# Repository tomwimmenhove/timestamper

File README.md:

# The Timestamper

This project lets you get get exact timestamps of 'events' (electric pulses on an input).

## Hardware
The hardware (schematic and PCB) are designed in KiCad 5, and can be found in the ./hardware/cpld/ directory. The 'heart'
of the design is a Xilinx XC9572XL CPLD. This CPLD implements a capture-counter which timestamps the arrival of events
with a resolution of 10ns. This CPLD is programmed in VHDL using Xilinx's ISE 14.7 (https://www.xilinx.com/support/download/index.html/content/xilinx/en/downloadNav/design-tools/v2012_4---14_7.html).

The VHDL project resides in the ./hardware/cpld/ directory. The XC9572XL can be programmed using the xc3sprog (http://xc3sprog.sourceforge.net/) utility.
Both the 'ft232h' (with a serial FT232H UART chip) and the 'sysfsgpio' (sysfsgpio on the Raspberry Pi) have been
successfully used to program the chip.

## Firmware
The firmware runs on an Atmel Atmega328p, which makes it compatible with the arduino. This way, using the default bootloader for,
for example, the Arduino pro mini 3.3v @8Mhz, we can easily program the firmware using avrdude. The firmware simply reads the
captured values from the CPLD and passes them on to a CH340G serial to USB UART. The firmware can be found in ./firmware/atmega328/

## Software
The software just outputs the values from the device onto stdout. See ./software/

# Theory of operation
The board is fed 3 signals:
 - A (very stable) 10MHz reference clock (I.E. from an OCXO or atomic rubidium reference)
 - A precise PPS signal, indicating the start of a UTC second. (I.E. from a GPS timing receiver)
 - An event signal that needs to be precisely timestamped.
 
 The 10Mhz is fed into a PLL (A Texas Instruments CDCE925), and multiplied to 100MHz, which is then fed to the CPLD.
 Inside the CPLD, this clocks a 27-bit counter. This counter is (synchronously) reset on the rising edge of the PPS
 signal. The event signal is sampled at every clock pulse, and when a rising-edge is detected, the current count is stored
 inside into a register and the capture counter is 'disarmed'. The CPLD then notifies the Atmega328P through an interrupt
 which, in turn, reads the value from the CPLD, places it in a buffer, and instructs the CPLD te re-arm the capture logic.
 The capture value is then simply sent out of the USB UART to the PC. We now have the fractional part of the timestamp on
 the PC. This can be combined with the current time on the PC to form a complete timestamp.
 NOTE: This assumes that the time on the PC that is reading the timestamps is well within a 500ms tolerance.
 
 # Links and other stuff
 See https://www.febo.com/pages/soekris/ for details on making an accurate NTP server.
 In addition, a Motorola m12+ GPS timing receiver together with a saw-tooth correction circuit is used to provide both a
 UTC time-source for the NTP server, as well as a PPS pulse for the Timestamper board.
 The Timestamper board also contains an 'auxiliary' output, which could be programmed to output a 33MHz clock that could
 be fed into the Soekris' motherboard to provide an even more accurate NTP time source (untested).

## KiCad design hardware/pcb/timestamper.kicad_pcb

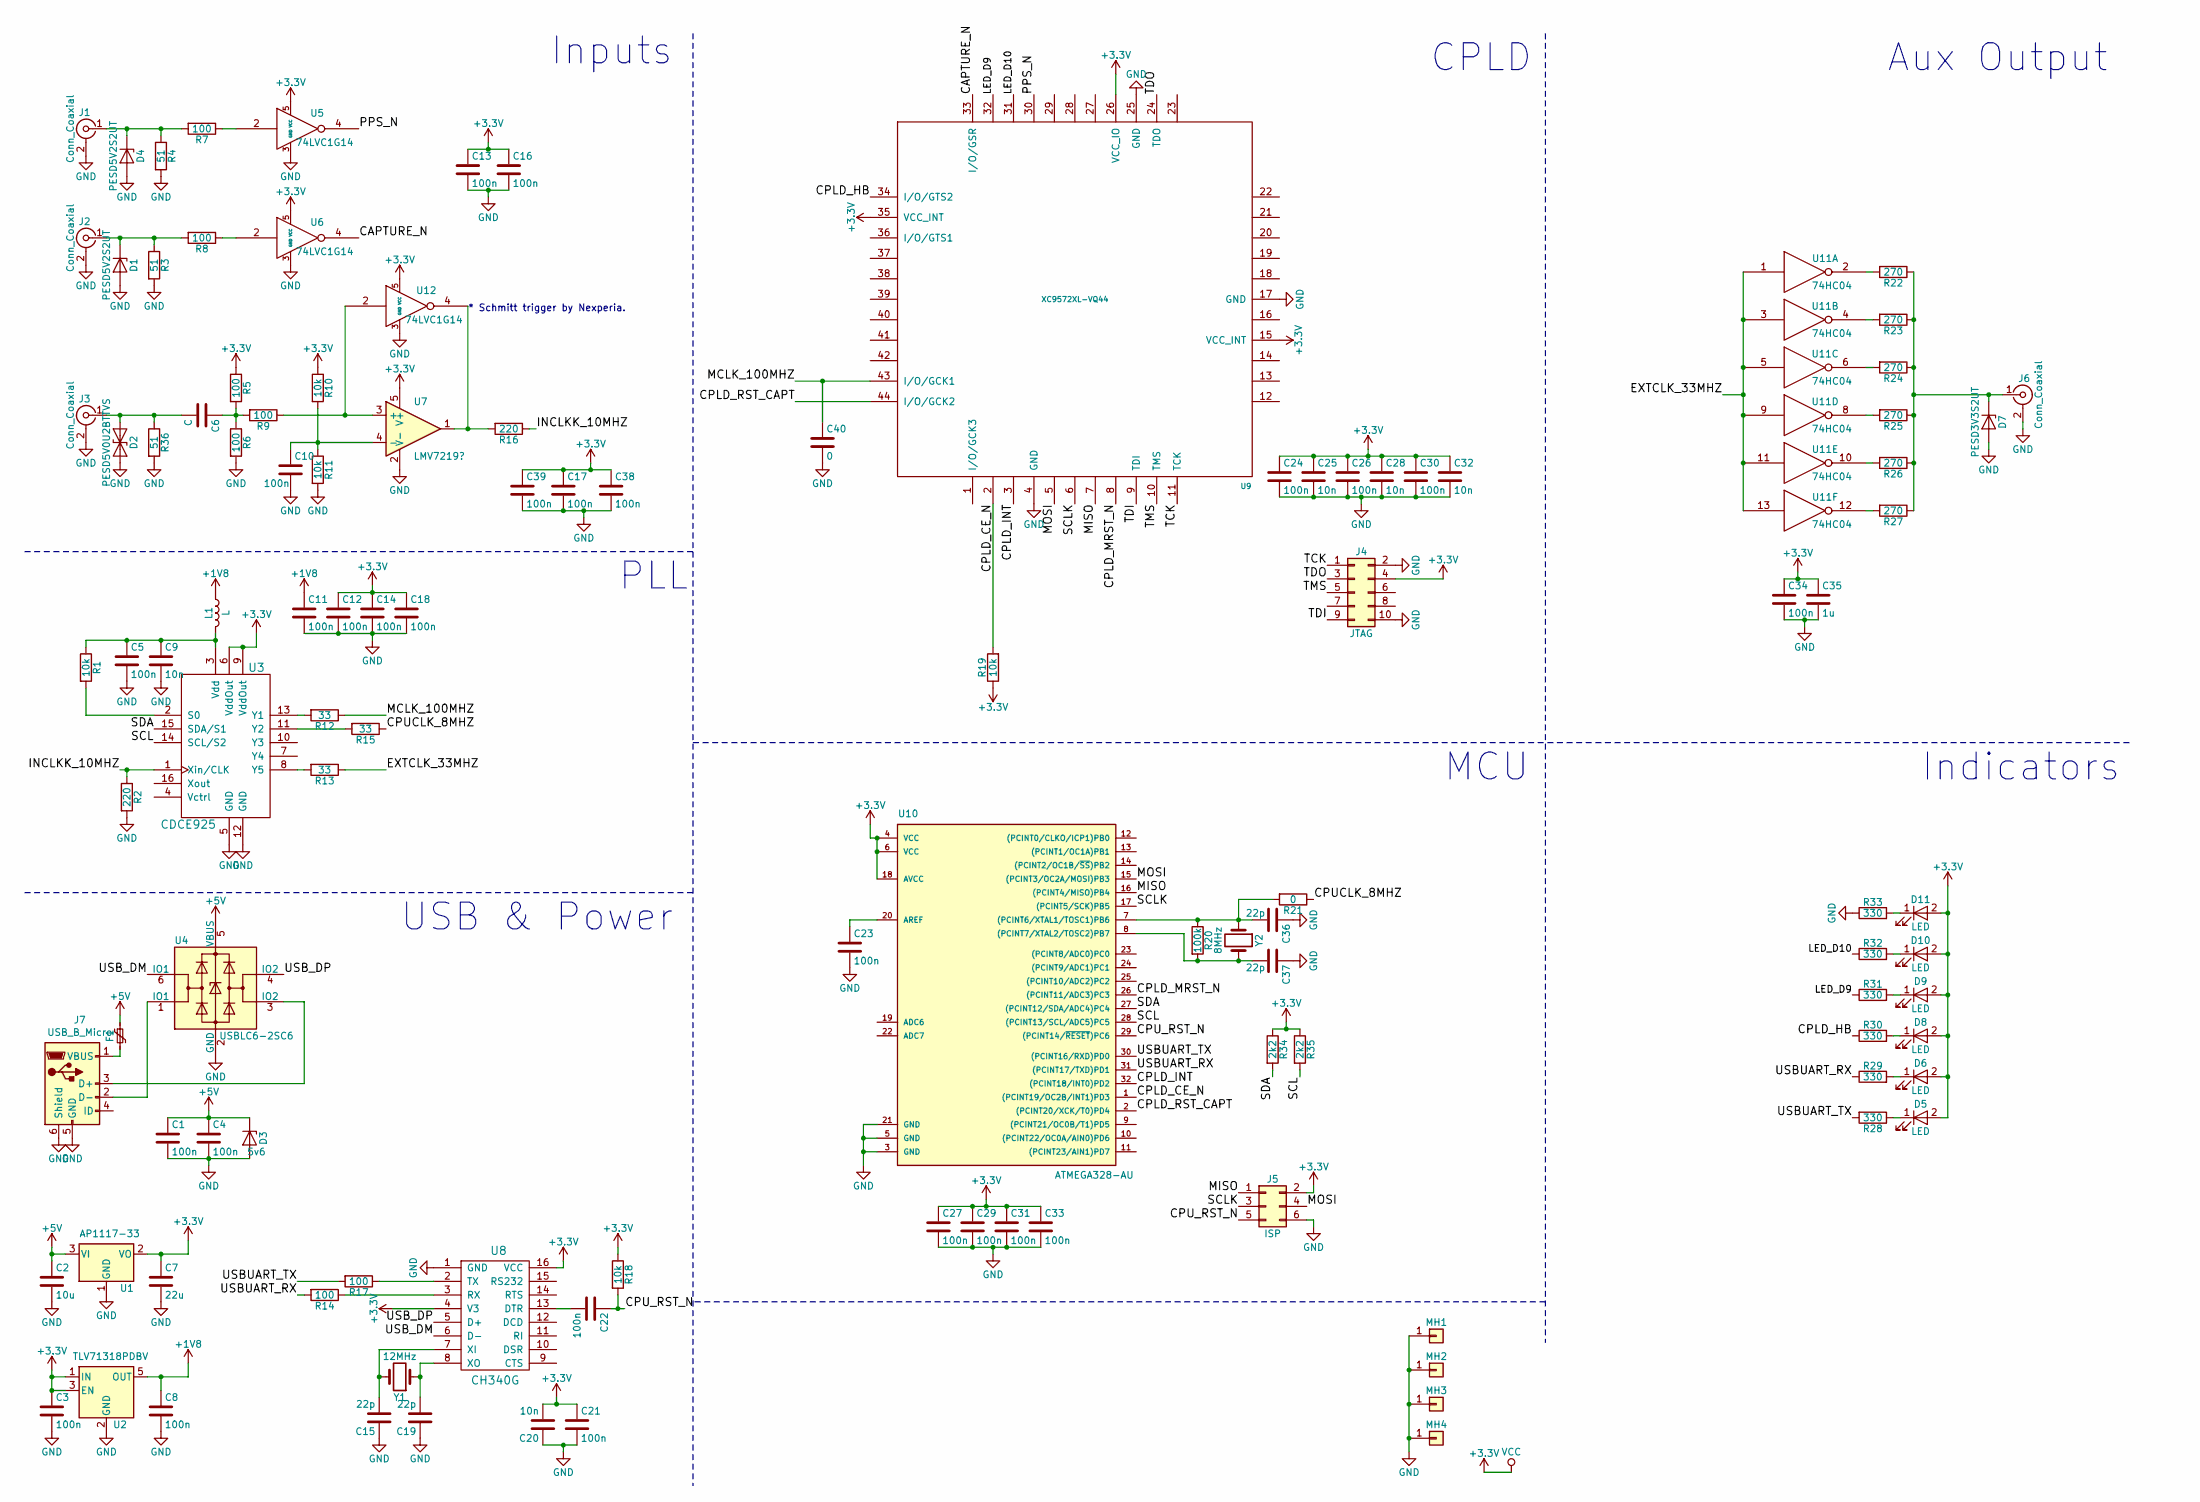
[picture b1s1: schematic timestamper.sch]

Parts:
C1, C3, C4, C5, C8, C10, C11, C12, C13, C14, C16, C17, C18, C21, C22, C23, C24, C26, C27, C29, C30, C31, C33, C34, C38, C39: 100n; C_0603_1608Metric
C2: 10u; C_0603_1608Metric
C6: C; C_0603_1608Metric
C7: 22u; C_0805_2012Metric
C9, C20, C25, C28, C32: 10n; C_0603_1608Metric
C15, C19, C36, C37: 22p; C_0603_1608Metric
C35: 1u; C_0603_1608Metric
C40: 0; C_0603_1608Metric
D1, D4: PESD5V2S2UT; D_SOT-23_NKA
D2: PESD5V0U2BTTVS; D_0603_1608Metric
D3: 5v6; D_SMB
D5, D6, D8, D9, D10, D11: LED; LED_0603_1608Metric
D7: PESD3V3S2UT; D_SOT-23_NKA
F1: Polyfuse_Small; R_1206_3216Metric
J1, J2, J3, J6: Conn_Coaxial; Molex_SMA_Jack_Edge_Mount
J4: JTAG; IDC-Header_2x05_P2.54mm_Vertical
J5: ISP; IDC-Header_2x03_P2.54mm_Vertical
J7: USB_B_Micro; USB_Micro-B_Molex_47346-0001
L1: L; L_0603_1608Metric
MH1, MH2, MH3, MH4: Conn_01x01; MountingHole_3.2mm_M3_Pad
R1, R10, R11, R18, R19: 10k; R_0603_1608Metric
R2, R16: 220; R_0603_1608Metric
R3, R4, R36: 51; R_0805_2012Metric
R5, R6, R7, R8, R9, R14, R17: 100; R_0603_1608Metric
R12, R13, R15: 33; R_0603_1608Metric
R20: 100k; R_0603_1608Metric
R21: 0; R_0603_1608Metric
R22, R23, R24, R25, R26, R27: 270; R_0603_1608Metric
R28, R29, R30, R31, R32, R33: 330; R_0603_1608Metric
R34, R35: 2k2; R_0603_1608Metric
U1: AP1117-33; SOT-223-3_TabPin2
U2: TLV71318PDBV; SOT-23-5
U3: CDCE925; TSSOP-16_4.4x5mm_P0.65mm
U4: USBLC6-2SC6; SOT-23-6
U5, U6, U12: 74LVC1G14; SOT-353_SC-70-5
U7: LMV7219?; SOT-23-5
U8: CH340G; SOIC-16_3.9x9.9mm_P1.27mm
U9: XC9572XL-VQ44; PQFP-44_10x10mm_P0.8mm
U10: ATMEGA328-AU; TQFP-32_7x7mm_P0.8mm
U11: 74HC04; TSSOP-14_4.4x5mm_P0.65mm
Y1: 12MHz; Crystal_HC49-4H_Vertical
Y2: 8MHz; Crystal_HC49-4H_Vertical

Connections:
+1V8: C8.1, C11.1, L1.1, U2.5 (OUT)
+3V3: C3.1, C7.1, C12.1, C13.1, C14.1, C16.1, C17.1, C18.1, C20.2, C21.1, C24.1, C25.1, C26.1, C27.1, C28.1, C29.1, C30.1, C31.1, C32.1, C33.1, C34.1, C35.1, C38.1, C39.1, D5.2 (A), D6.2 (A), D8.2 (A), D9.2 (A), D10.2 (A), D11.2 (A), J4.4, J5.2, R5.1, R10.1, R18.1, R19.1, R34.1, R35.1, U1.2 (VO), U2.1 (IN), U2.3 (EN), U3.6 (VddOut), U3.9 (VddOut), U5.5 (VCC), U6.5 (VCC), U7.5 (V+), U8.4 (V3), U8.16 (VCC), U9.15 (VCC_INT), U9.26 (VCC_IO), U9.35 (VCC_INT), U10.4 (VCC), U10.6 (VCC), U10.18 (AVCC), U11.14 (VCC), U12.5 (VCC)
+5V: C1.1, C2.1, C4.1, D3.1 (K), F1.1, U1.3 (VI), U4.5 (VBUS)
/CAPTURE_N: U6.4, U9.33 (I/O/GSR)
/CPLD_CE_N: R19.2, U9.2, U10.1 ((PCINT19/OC2B/INT1)PD3)
/CPLD_HB: R30.1, U9.34 (I/O/GTS2)
/CPLD_INT: U9.3, U10.32 ((PCINT18/INT0)PD2)
/CPLD_MRST_N: U9.8, U10.26 ((PCINT11/ADC3)PC3)
/CPLD_RST_CAPT: U9.44 (I/O/GCK2), U10.2 ((PCINT20/XCK/T0)PD4)
/CPUCLK_8MHZ: R15.1, R21.1
/CPU_RST_N: C22.1, J5.5, R18.2, U10.29 ((PCINT14/~RESET~)PC6)
/EXTCLK_33MHZ: R13.1, U11.1, U11.3, U11.5, U11.9, U11.11, U11.13
/INCLKK_10MHZ: R2.1, R16.1, U3.1 (Xin/CLK)
/LED_D9: R31.1, U9.32
/LED_D10: R32.1, U9.31
/MCLK_100MHZ: C40.1, R12.1, U9.43 (I/O/GCK1)
/MISO: J5.1, U9.7, U10.16 ((PCINT4/MISO)PB4)
/MOSI: J5.4, U9.5, U10.15 ((PCINT3/OC2A/MOSI)PB3)
/PPS_N: U5.4, U9.30
/SCL: R35.2, U3.14 (SCL/S2), U10.28 ((PCINT13/SCL/ADC5)PC5)
/SCLK: J5.3, U9.6, U10.17 ((PCINT5/SCK)PB5)
/SDA: R34.2, U3.15 (SDA/S1), U10.27 ((PCINT12/SDA/ADC4)PC4)
/TCK: J4.1, U9.11 (TCK)
/TDI: J4.9, U9.9 (TDI)
/TDO: J4.3, U9.24 (TDO)
/TMS: J4.5, U9.10 (TMS)
/USBUART_RX: R14.2, R29.1, U10.31 ((PCINT17/TXD)PD1)
/USBUART_TX: R17.2, R28.2, U10.30 ((PCINT16/RXD)PD0)
/USB_DM: U4.6 (IO1), U8.6 (D-)
/USB_DP: U4.4 (IO2), U8.5 (D+)
GND: C1.2, C2.2, C3.2, C4.2, C5.2, C7.2, C8.2, C9.2, C10.2, C11.2, C12.2, C13.2, C14.2, C15.1, C16.2, C17.2, C18.2, C19.1, C20.1, C21.2, C23.2, C24.2, C25.2, C26.2, C27.2, C28.2, C29.2, C30.2, C31.2, C32.2, C33.2, C34.2, C35.2, C36.1, C37.1, C38.2, C39.2, C40.2, D1.2 (A), D2.2 (A2), D3.2 (A), D4.2 (A), D7.2 (A), J1.2 (Ext), J2.2 (Ext), J3.2 (Ext), J4.2, J4.10, J5.6, J6.2 (Ext), J7.5 (GND), J7.6 (Shield), MH1.1, MH2.1, MH3.1, MH4.1, R2.2, R3.2, R4.2, R6.2, R11.2, R33.1, R36.2, U1.1 (GND), U2.2 (GND), U3.5 (GND), U3.12 (GND), U4.2 (GND), U5.3 (GND), U6.3 (GND), U7.2 (V-), U8.1 (GND), U9.4 (GND), U9.17 (GND), U9.25 (GND), U10.3 (GND), U10.5 (GND), U10.21 (GND), U11.7 (GND), U12.3 (GND)
unnamed: C5.1, C9.1, L1.2, R1.1, U3.3 (Vdd)
unnamed: C6.1, R5.2, R6.1, R9.2
unnamed: C6.2, D2.1 (A1), J3.1 (In), R36.1
unnamed: C10.1, R10.2, R11.1, U7.4 (-)
unnamed: C15.2, U8.7 (XI), Y1.2
unnamed: C19.2, U8.8 (XO), Y1.1
unnamed: C22.2, U8.13 (DTR)
unnamed: C23.1, U10.20 (AREF)
unnamed: C36.2, R20.1, R21.2, U10.7 ((PCINT6/XTAL1/TOSC1)PB6), Y2.1
unnamed: C37.2, R20.2, U10.8 ((PCINT7/XTAL2/TOSC2)PB7), Y2.2
unnamed: D1.1 (K), J2.1 (In), R3.1, R8.2
unnamed: D4.1 (K), J1.1 (In), R4.1, R7.2
unnamed: D5.1 (K), R28.1
unnamed: D6.1 (K), R29.2
unnamed: D7.1 (K), J6.1 (In), R22.1, R23.1, R24.1, R25.1, R26.1, R27.1
unnamed: D8.1 (K), R30.2
unnamed: D9.1 (K), R31.2
unnamed: D10.1 (K), R32.2
unnamed: D11.1 (K), R33.2
unnamed: F1.2, J7.1 (VBUS)
unnamed: J7.2 (D-), U4.1 (IO1)
unnamed: J7.3 (D+), U4.3 (IO2)
unnamed: R1.2, U3.2 (S0)
unnamed: R7.1, U5.2
unnamed: R8.1, U6.2
unnamed: R9.1, U7.3 (+), U12.2
unnamed: R12.2, U3.13 (Y1)
unnamed: R13.2, U3.8 (Y5)
unnamed: R14.1, U8.3 (RX)
unnamed: R15.2, U3.11 (Y2)
unnamed: R16.2, U7.1, U12.4
unnamed: R17.1, U8.2 (TX)
unnamed: R22.2, U11.2
unnamed: R23.2, U11.4
unnamed: R24.2, U11.6
unnamed: R25.2, U11.8
unnamed: R26.2, U11.10
unnamed: R27.2, U11.12

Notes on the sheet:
Indicators
Aux Output
CPLD
MCU
Inputs
PLL
USB & Power
* Schmitt trigger by Nexperia.

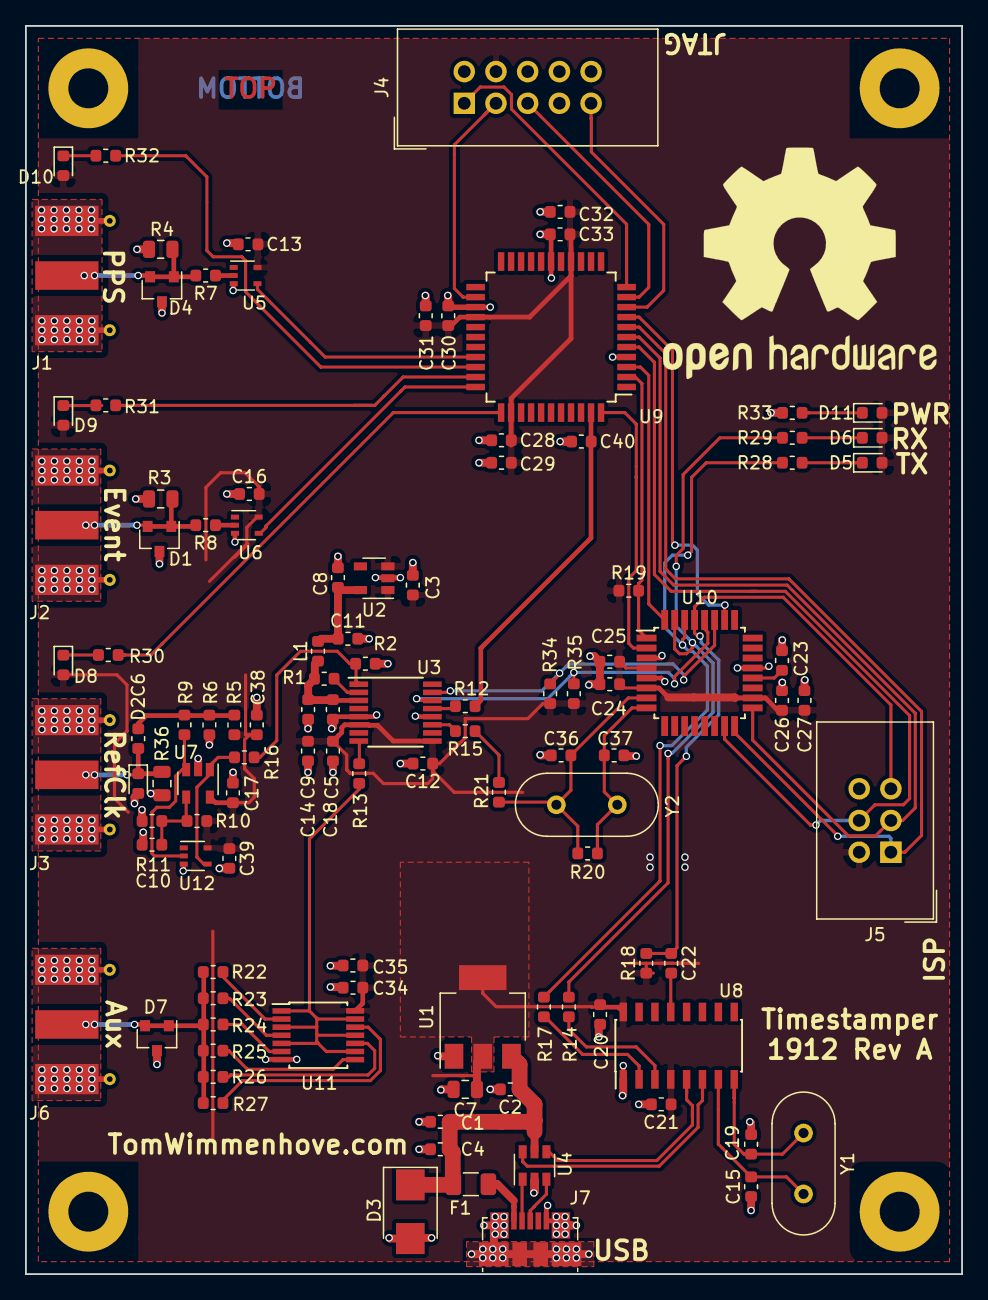
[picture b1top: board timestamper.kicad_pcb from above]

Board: 2 copper layers, 75.0 x 100.0 mm, 114 parts (0 on the bottom side), 69 nets.

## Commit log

2019-03-01 Byte align the counter value
2019-03-02 Don't leep counter in reset during PPS
2019-03-02 Added test benches
2019-03-02 Added master reset. Rewrote main tb in vhdl
2019-03-02 Converted to lower case
2019-03-02 cleanup
2019-03-02 Added licence
2019-03-03 Added _in and _out postfixes
2019-03-03 bmux was too wide
2019-03-07 Works in harwdware - backup
2019-03-12 Works on hardware
2019-03-12 Moved all CPLD related files
2019-03-12 Added KiCad pcb project
2019-03-12 Added arduino/atmel firmware
2019-03-12 Added cdce925 TI Clock Pro files
2019-03-12 Fixed after relocating KiCad project
2019-03-12 Added main.ucf file
2019-03-13 Initial component placement
2019-03-13 Upgraded to KiCad 5.0
2019-03-13 Changed some libraries
2019-03-14 backup
2019-03-14 Updated R and C footprints
2019-03-14 Updated all footprints
2019-03-14 Finished most of routing
2019-03-15 Synched pinouts between CPLD and PCB
2019-03-15 Moved refdesses, added silk-screen anotations
2019-03-15 Forgot to change L1 footprint
2019-03-15 Added SMA 3d model
2019-03-15 Added silk-screen comments
2019-03-15 Moved licence to correct place
2019-03-15 Minor schematic cleanup
2019-03-15 Fixed CH340G (U8) foot print
2019-03-16 Added optional schmitt input on refclk
2019-03-17 Ground via insanity reduction
2019-03-17 VCC plane on top
2019-03-17 Small fixes
2019-03-17 Minor cleanup
2019-03-18 Fixed mask clearance. Keep-out around mounting holes
2019-03-20 Replaced arduino with native avr project
2019-03-20 Made interrupt line active low
2019-03-20 Some cleanup
2019-03-20 Fixed buffer
2019-03-20 Using FTDI FT232H JTAG programmer
2019-03-21 Some more cleaning up
2019-03-21 Final changes before first board spin
2019-03-23 Fixed VHD bug where capture would misfire due to atmel laginess
2019-03-23 Changed comm-protocol. Added reader 'client'
2019-03-23 Added uart_puts() for testing
2019-03-23 Added simple udev rule for consistent (with a single CH340) device naming
2019-03-23 Added a readme
2019-03-24 Convert capture value to actual time and date timestamp
2019-03-24 Forgot to use modulus of capture count
2019-03-24 Fixed-point bugfix. ttyUSB flush bugfix
2019-03-24 Small formatting change
2019-03-24 Improved serial communication
2019-03-24 Check if capture-count is above 100M (plus tolerance)
2019-03-24 Added makefile for timestamper client program
2019-03-24 Added simple debugging tool skip system clock ahead/back a number of microseconds
2019-03-24 Very minor cleanup
2019-03-25 Make install and uninstall
2019-03-25 Support 76800 baud-rate
2019-03-28 Working with first board spin!
2019-03-30 Added 3D printable enclosure
2019-03-30 Added GNU headers
2019-03-30 Added Pictures
2019-03-30 Scaled Image
2019-03-30 Forgot GPL headers in VHDL project
2019-03-30 Configurable PLL frequency. Fixes #4
2019-03-30 Atmel firmware Makefile project uses "TI Clock Pro" output for PLL settings
2019-03-30 Avoid interrupts when buffer is full
2019-03-30 Forgot to update 'unreliable' offset after change to nanoseconds
2019-03-30 More sensible bit packing
2019-03-31 Read PLL configuration at run-time. Make reference clock configurable from command-line
2019-03-31 Temporary hacky fix for stupid serial comm bug
2019-04-01 Made PLL (sysclk and aux) configurable from comman-line
2019-04-01 Negative error printing bug
2019-04-01 Forgot to add GPL headers to new source files
2019-04-04 Added some debugging options
2019-04-05 Fixed embarrassing serial port comms bug
2019-04-05 Always flush after you're done
2019-04-06 Added ability to add offset to timestamp
